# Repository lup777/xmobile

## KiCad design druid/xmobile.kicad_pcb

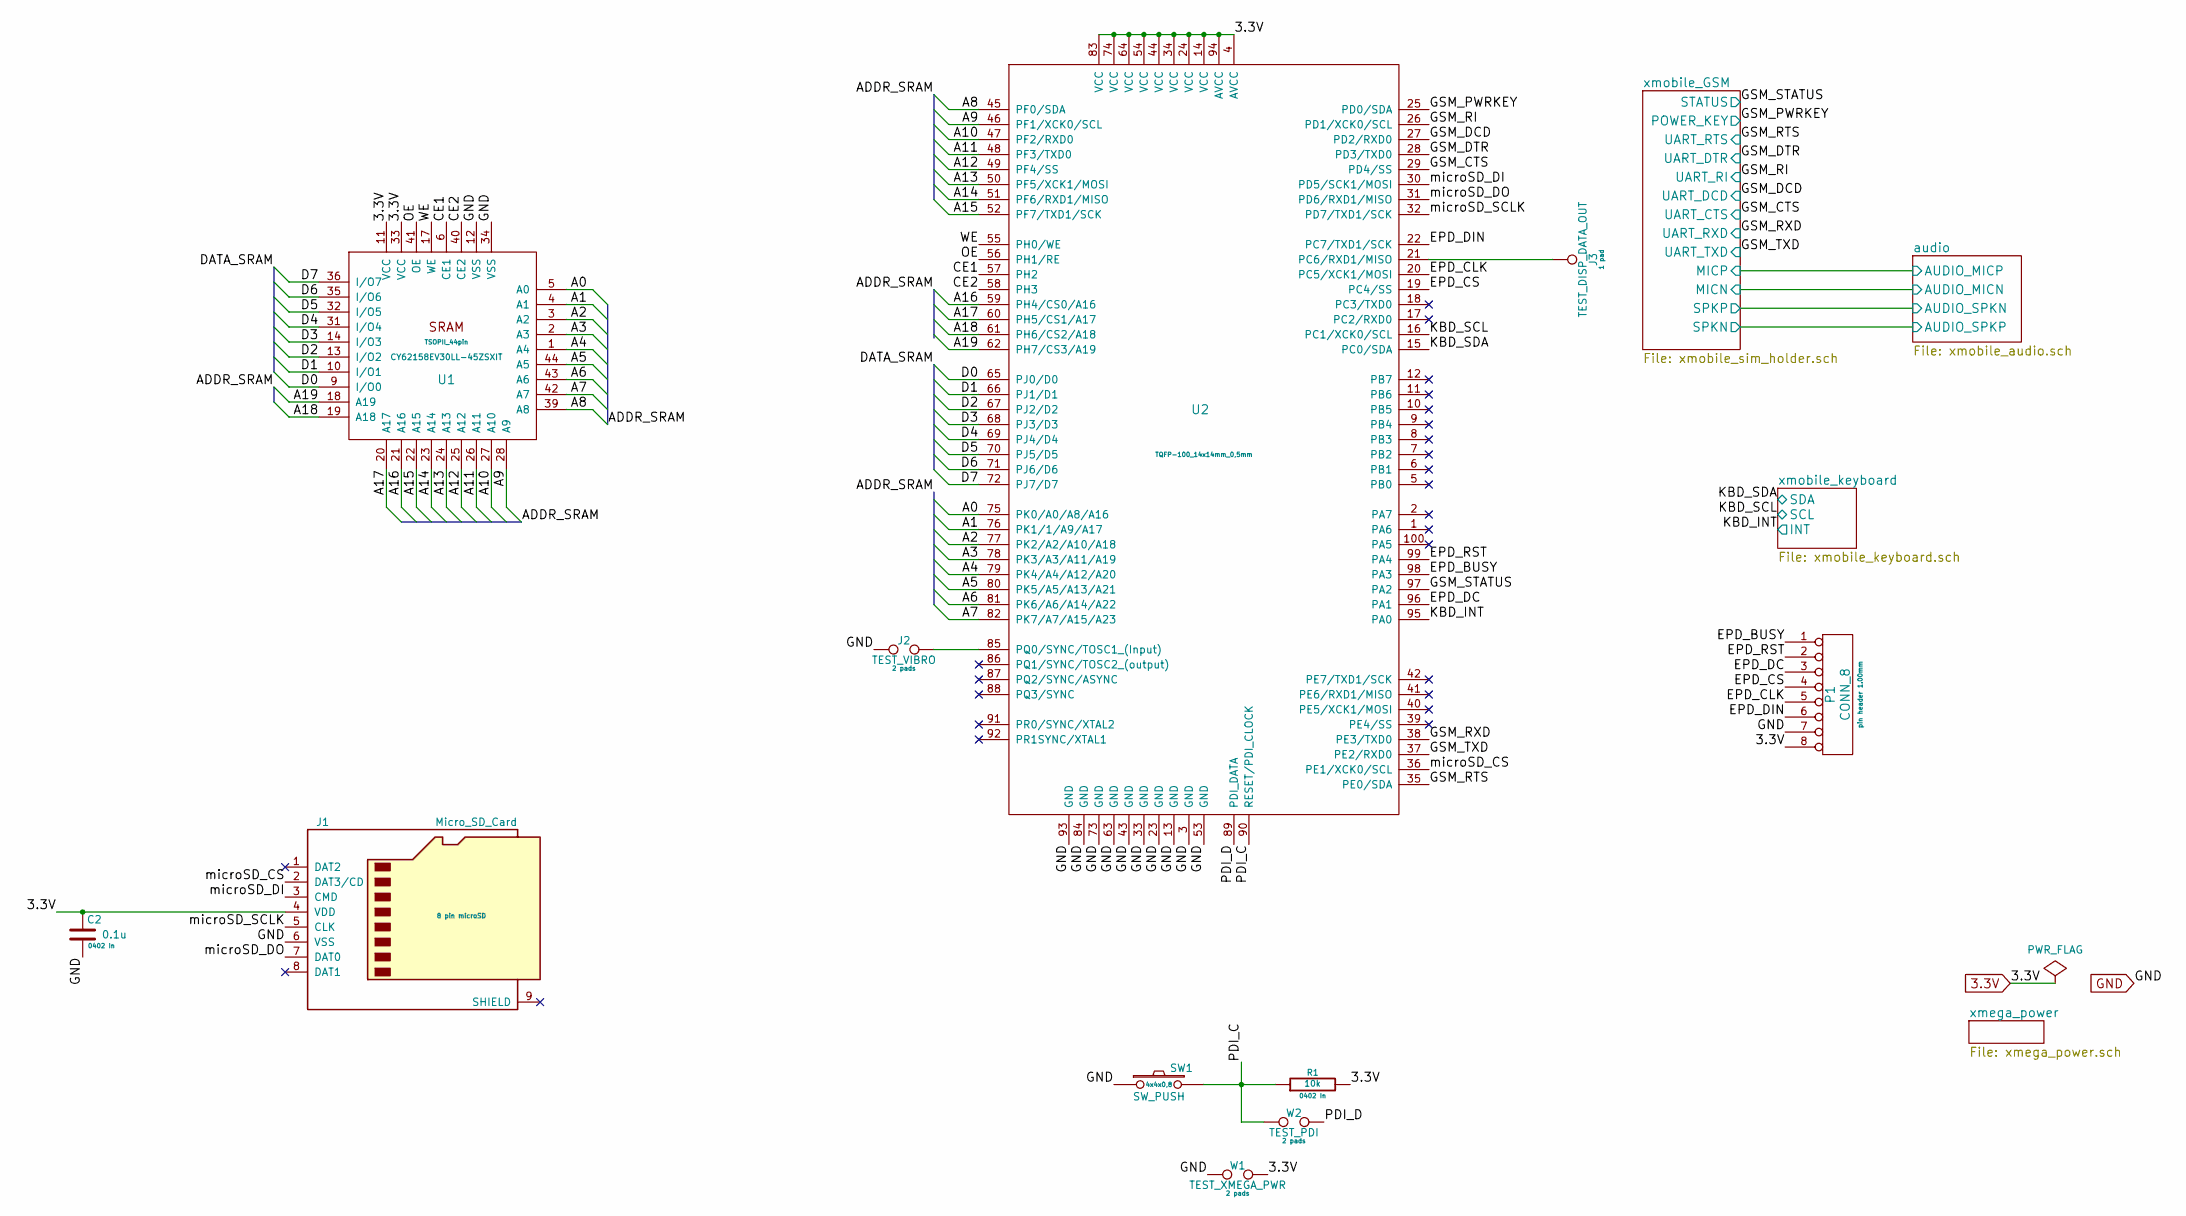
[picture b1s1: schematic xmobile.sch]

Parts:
C2: 0.1u; C_0402_1005Metric
J1: Micro_SD_Card; microSD_HC_Wuerth_693072010801
J2: TEST_VIBRO; TestPoint_2Pads_Pitch2.54mm_Drill0.8mm
J3: TEST_DISP_DATA_OUT; TestPoint_THTPad_1.0x1.0mm_Drill0.5mm
P1: CONN_8; PinHeader_1x08_P1.00mm_Vertical
R1: 10k; R_0402_1005Metric
SW1: SW_PUSH; button_4pin_7,5x5
U1: CY62158EV30LL-45ZSXIT; TSOPII_44_pin
U2: XMega128A1U_TQFP100; TQFP-100_14x14mm_P0.5mm
W1: TEST_XMEGA_PWR; TestPoint_2Pads_Pitch2.54mm_Drill0.8mm
W2: TEST_PDI; TestPoint_2Pads_Pitch2.54mm_Drill0.8mm

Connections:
3.3V: C2.1, J1.4 (VDD), P1.8, R1.2, U1.11 (VCC), U1.33 (VCC), U2.4 (AVCC), U2.14 (VCC), U2.24 (VCC), U2.34 (VCC), U2.44 (VCC), U2.54 (VCC), U2.64 (VCC), U2.74 (VCC), U2.83 (VCC), U2.94 (AVCC), W1.2; also elsewhere on the board
/A0: U1.5 (A0), U2.75 (PK0/A0/A8/A16)
/A1: U1.4 (A1), U2.76 (PK1/1/A9/A17)
/A2: U1.3 (A2), U2.77 (PK2/A2/A10/A18)
/A3: U1.2 (A3), U2.78 (PK3/A3/A11/A19)
/A4: U1.1 (A4), U2.79 (PK4/A4/A12/A20)
/A5: U1.44 (A5), U2.80 (PK5/A5/A13/A21)
/A6: U1.43 (A6), U2.81 (PK6/A6/A14/A22)
/A7: U1.42 (A7), U2.82 (PK7/A7/A15/A23)
/A8: U1.39 (A8), U2.45 (PF0/SDA)
/A9: U1.28 (A9), U2.46 (PF1/XCK0/SCL)
/A10: U1.27 (A10), U2.47 (PF2/RXD0)
/A11: U1.26 (A11), U2.48 (PF3/TXD0)
/A12: U1.25 (A12), U2.49 (PF4/SS)
/A13: U1.24 (A13), U2.50 (PF5/XCK1/MOSI)
/A14: U1.23 (A14), U2.51 (PF6/RXD1/MISO)
/A15: U1.22 (A15), U2.52 (PF7/TXD1/SCK)
/A16: U1.21 (A16), U2.59 (PH4/CS0/A16)
/A17: U1.20 (A17), U2.60 (PH5/CS1/A17)
/A18: U1.19 (A18), U2.61 (PH6/CS2/A18)
/A19: U1.18 (A19), U2.62 (PH7/CS3/A19)
/CE1: U1.6 (CE1), U2.57 (PH2)
/CE2: U1.40 (CE2), U2.58 (PH3)
/D0: U1.9 (I/O0), U2.65 (PJ0/D0)
/D1: U1.10 (I/O1), U2.66 (PJ1/D1)
/D2: U1.13 (I/O2), U2.67 (PJ2/D2)
/D3: U1.14 (I/O3), U2.68 (PJ3/D3)
/D4: U1.31 (I/O4), U2.69 (PJ4/D4)
/D5: U1.32 (I/O5), U2.70 (PJ5/D5)
/D6: U1.35 (I/O6), U2.71 (PJ6/D6)
/D7: U1.36 (I/O7), U2.72 (PJ7/D7)
/EPD_BUSY: P1.1, U2.98 (PA3); also elsewhere on the board
/EPD_CLK: P1.5, U2.20 (PC5/XCK1/MOSI); also elsewhere on the board
/EPD_CS: P1.4, U2.19 (PC4/SS); also elsewhere on the board
/EPD_DC: P1.3, U2.96 (PA1); also elsewhere on the board
/EPD_DIN: P1.6, U2.22 (PC7/TXD1/SCK); also elsewhere on the board
/EPD_RST: P1.2, U2.99 (PA4); also elsewhere on the board
/GSM_CTS: U2.29 (PD4/SS); also elsewhere on the board
/GSM_DCD: U2.27 (PD2/RXD0); also elsewhere on the board
/GSM_DTR: U2.28 (PD3/TXD0); also elsewhere on the board
/GSM_PWRKEY: U2.25 (PD0/SDA); also elsewhere on the board
/GSM_RI: U2.26 (PD1/XCK0/SCL); also elsewhere on the board
/GSM_RTS: U2.35 (PE0/SDA); also elsewhere on the board
/GSM_RXD: U2.38 (PE3/TXD0); also elsewhere on the board
/GSM_STATUS: U2.97 (PA2); also elsewhere on the board
/GSM_TXD: U2.37 (PE2/RXD0); also elsewhere on the board
/KBD_INT: U2.95 (PA0); also elsewhere on the board
/KBD_SCL: U2.16 (PC1/XCK0/SCL); also elsewhere on the board
/KBD_SDA: U2.15 (PC0/SDA); also elsewhere on the board
/OE: U1.41 (OE), U2.56 (PH1/RE)
/PDI_C: R1.1, SW1.2, U2.90 (RESET/PDI_CLOCK), W2.1
/PDI_D: U2.89 (PDI_DATA), W2.2
/WE: U1.17 (WE), U2.55 (PH0/WE)
/microSD_CS: J1.2 (DAT3/CD), U2.36 (PE1/XCK0/SCL)
/microSD_DI: J1.3 (CMD), U2.30 (PD5/SCK1/MOSI)
/microSD_DO: J1.7 (DAT0), U2.31 (PD6/RXD1/MISO)
/microSD_SCLK: J1.5 (CLK), U2.32 (PD7/TXD1/SCK)
GND: C2.2, J1.6 (VSS), J2.1, P1.7, SW1.1, U1.12 (VSS), U1.34 (VSS), U2.3 (GND), U2.13 (GND), U2.23 (GND), U2.33 (GND), U2.43 (GND), U2.53 (GND), U2.63 (GND), U2.73 (GND), U2.84 (GND), U2.93 (GND), W1.1; also elsewhere on the board
unnamed: J2.2, U2.85 (PQ0/SYNC/TOSC1_(Input))
unnamed: J3.1, U2.21 (PC6/RXD1/MISO)

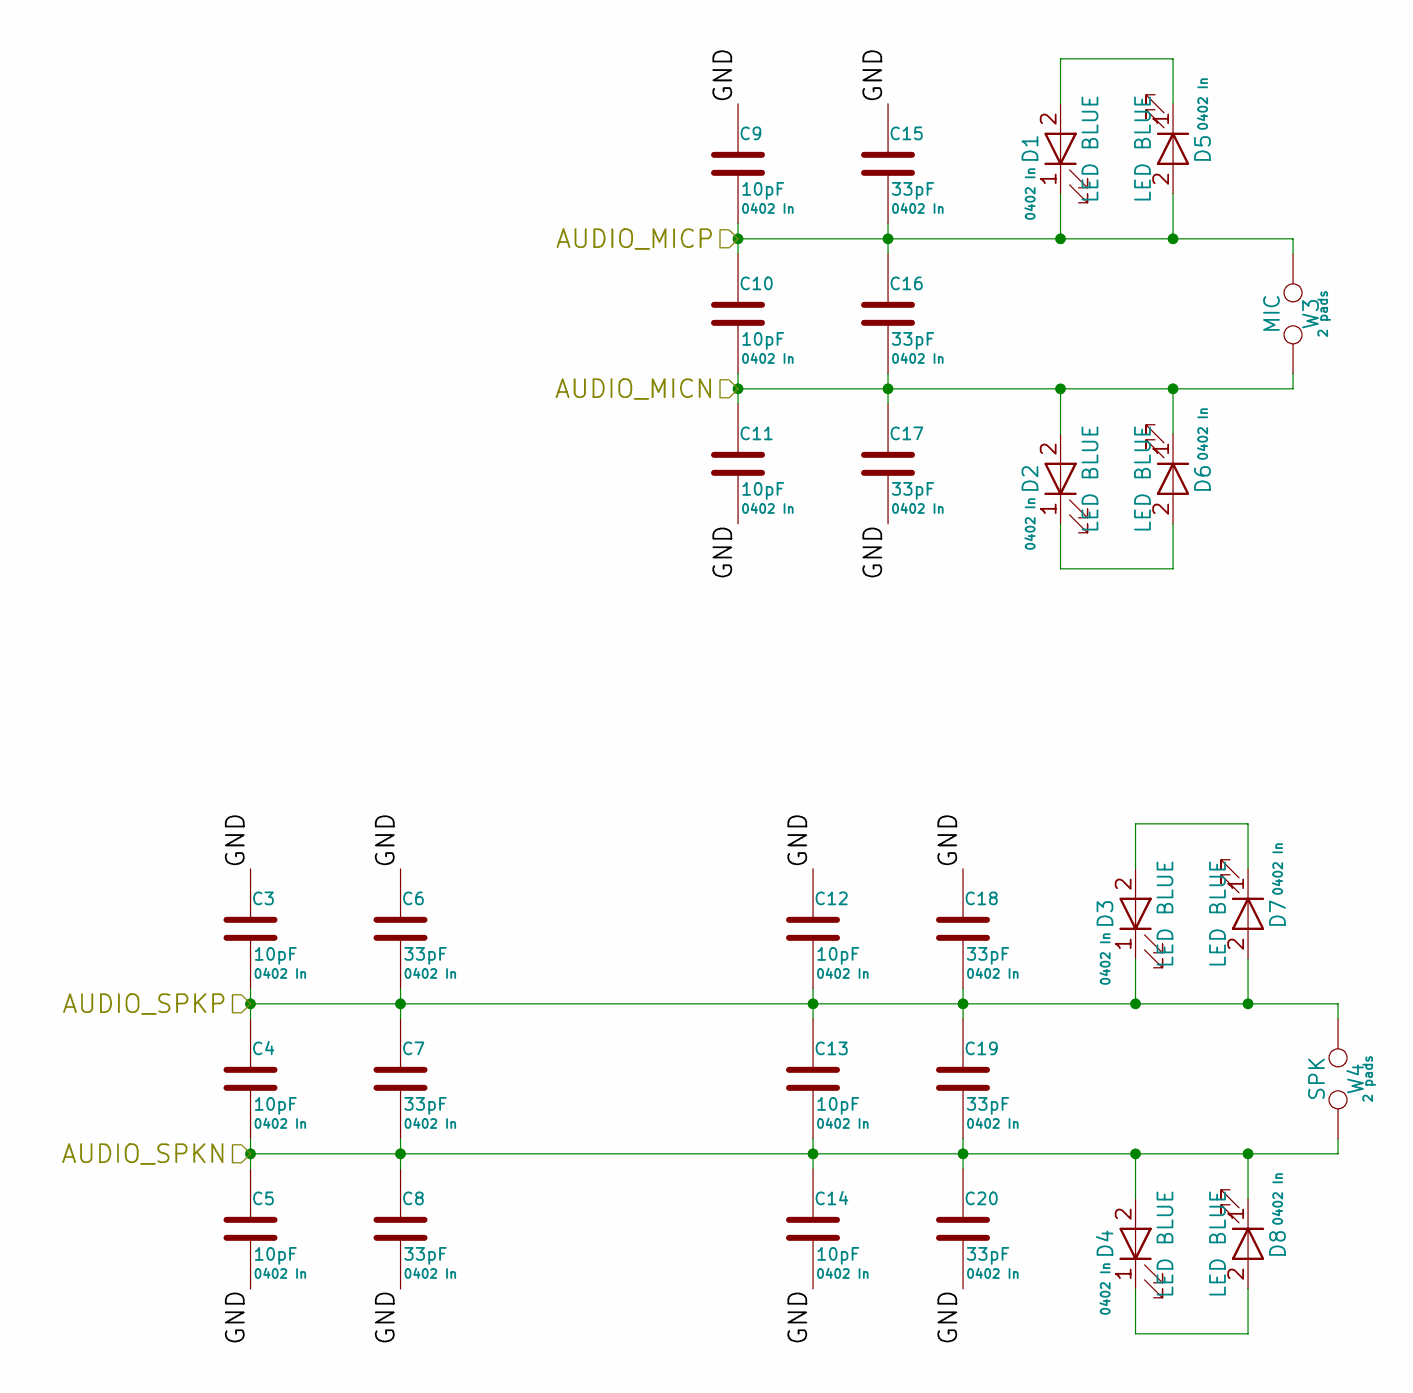
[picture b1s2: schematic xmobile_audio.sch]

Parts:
C3, C4, C5, C9, C10, C11, C12, C13, C14: 10pF; C_0402_1005Metric
C6, C7, C8, C15, C16, C17, C18, C19, C20: 33pF; C_0402_1005Metric
D1, D2, D3, D4, D5, D6, D7, D8: LED BLUE; LED_0402_1005Metric
W3: MIC; TestPoint_2Pads_Pitch2.54mm_Drill0.8mm
W4: SPK; TestPoint_2Pads_Pitch2.54mm_Drill0.8mm

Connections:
/audio/AUDIO_MICN: C10.2, C11.1, C16.2, C17.1, D2.2 (A), D6.1 (K), W3.2; also elsewhere on the board
/audio/AUDIO_MICP: C9.2, C10.1, C15.2, C16.1, D1.1 (K), D5.2 (A), W3.1; also elsewhere on the board
/audio/AUDIO_SPKN: C4.2, C5.1, C7.2, C8.1, C13.2, C14.1, C19.2, C20.1, D4.2 (A), D8.1 (K), W4.2; also elsewhere on the board
/audio/AUDIO_SPKP: C3.2, C4.1, C6.2, C7.1, C12.2, C13.1, C18.2, C19.1, D3.1 (K), D7.2 (A), W4.1; also elsewhere on the board
GND: C3.1, C5.2, C6.1, C8.2, C9.1, C11.2, C12.1, C14.2, C15.1, C17.2, C18.1, C20.2; also elsewhere on the board
unnamed: D1.2 (A), D5.1 (K)
unnamed: D2.1 (K), D6.2 (A)
unnamed: D3.2 (A), D7.1 (K)
unnamed: D4.1 (K), D8.2 (A)

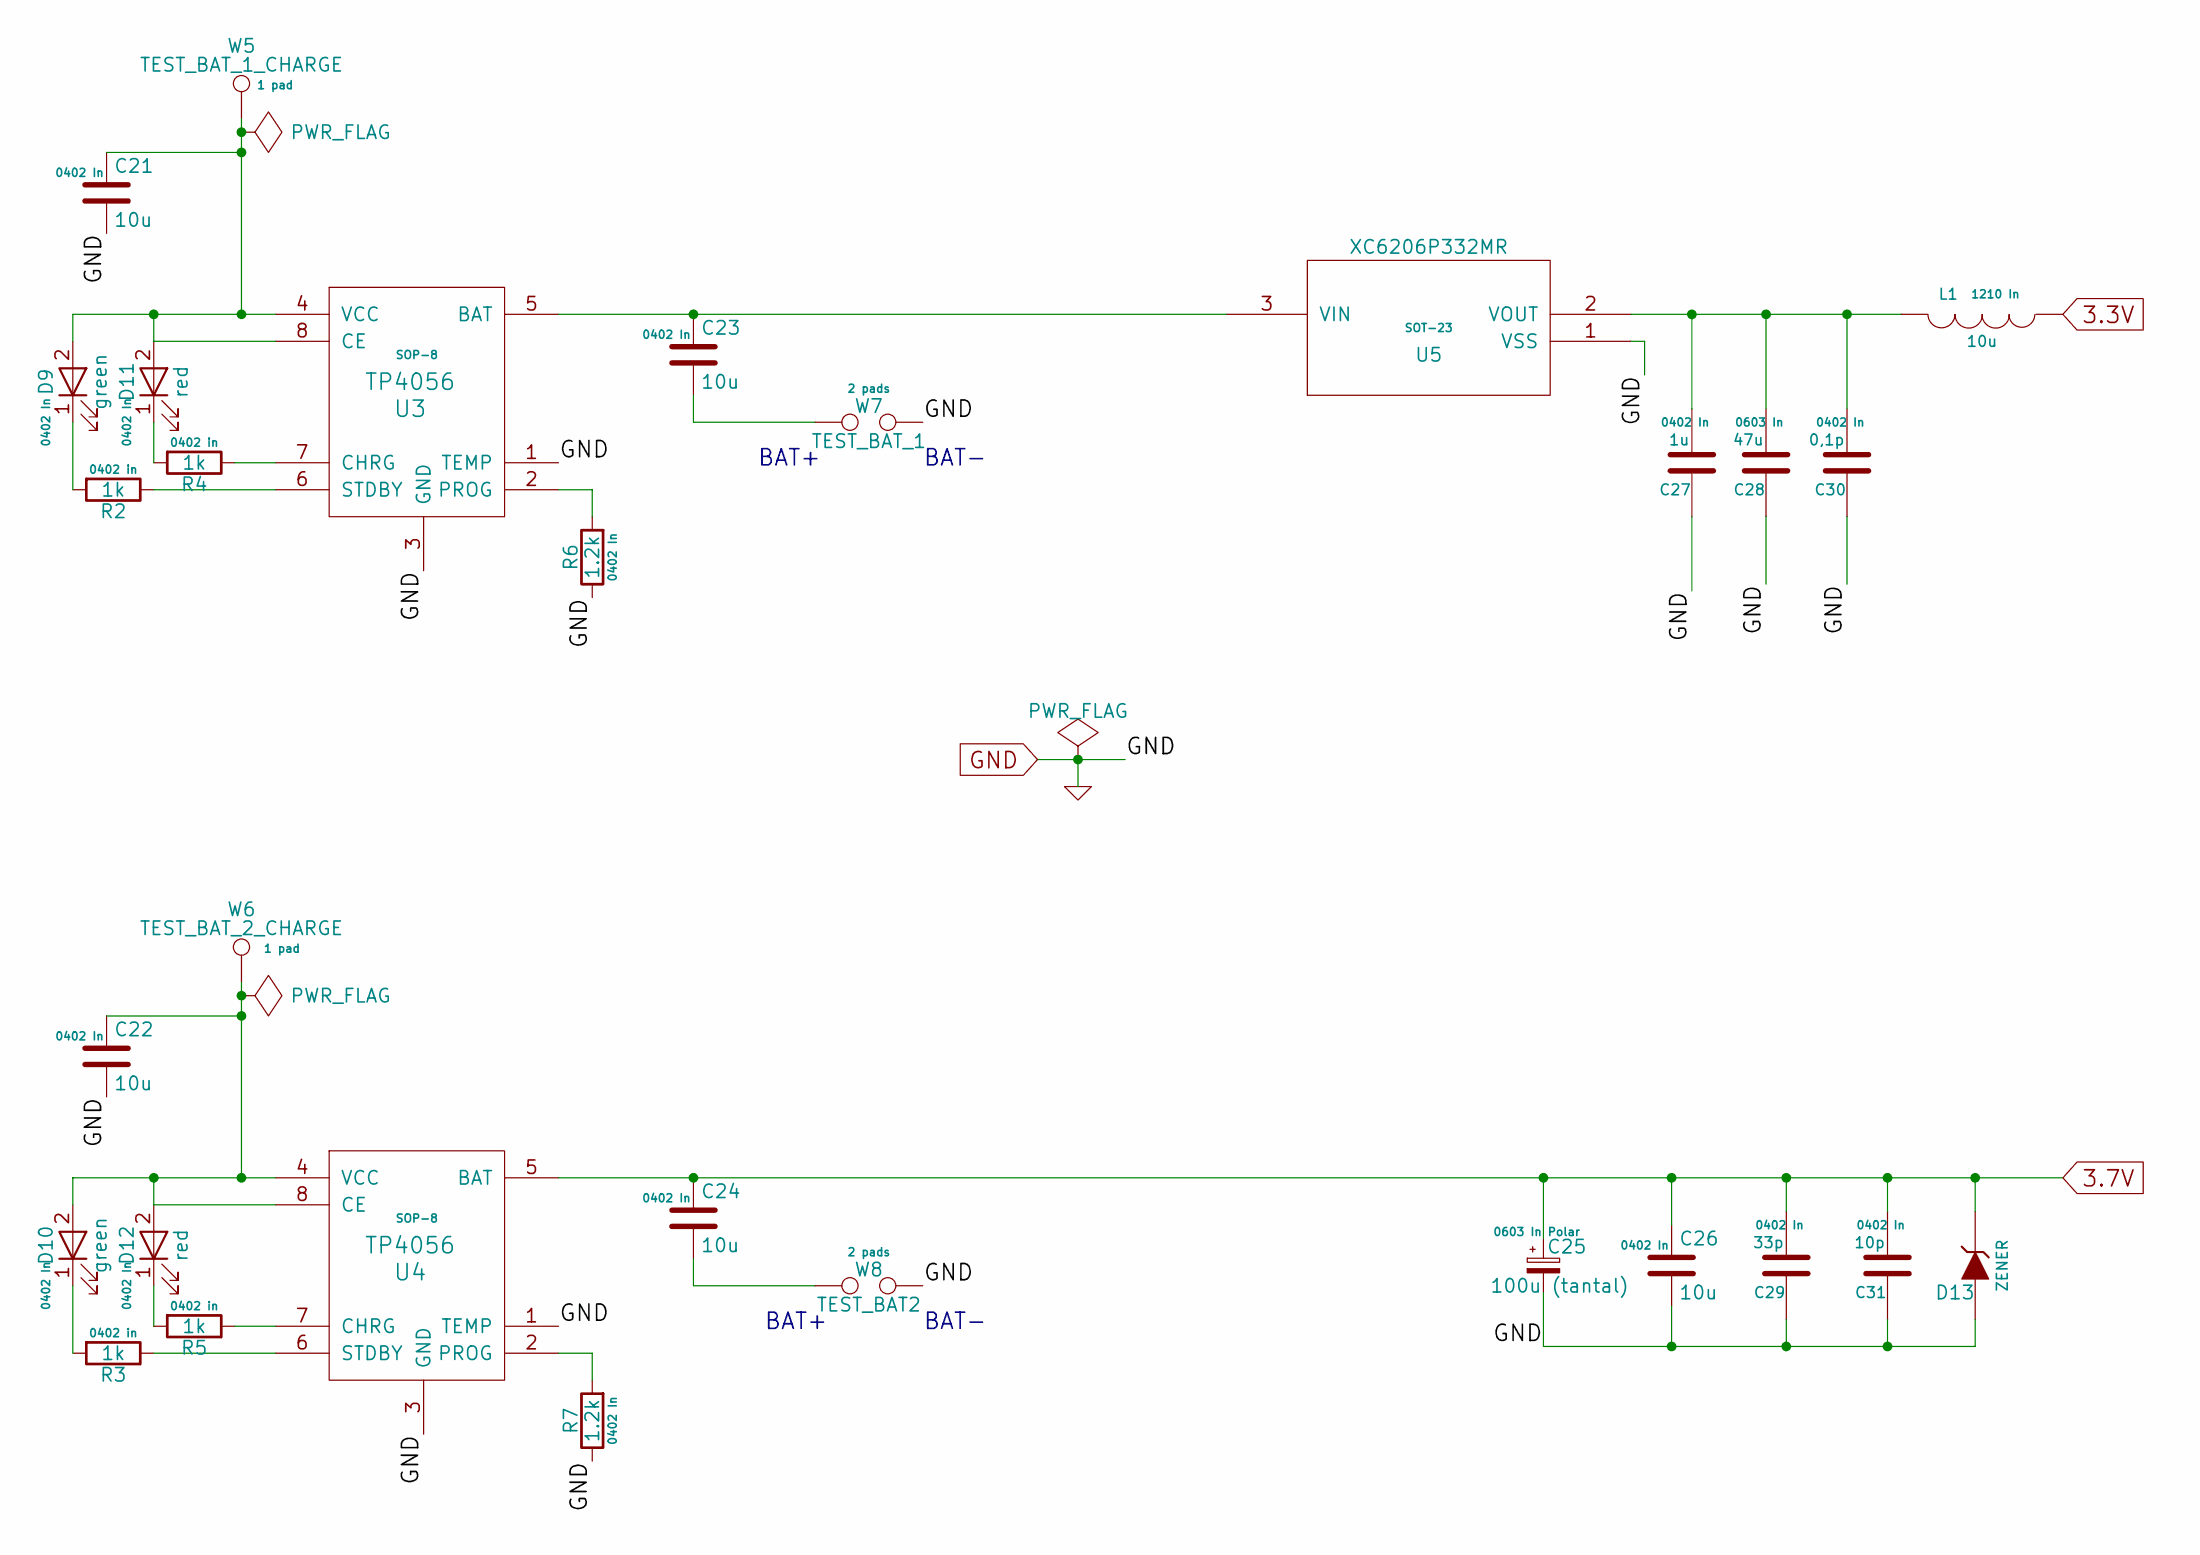
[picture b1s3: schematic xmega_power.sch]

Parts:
C21, C22, C23, C24, C26: 10u; C_0402
C25: 100u (tantal); C_0603
C27: 1u; C_0402
C28: 47u; C_0603
C29: 33p; C_0402
C30: 0,1p; C_0402
C31: 10p; C_0402
D9, D10: green; LED_0402
D11, D12: red; LED_0402
D13: ZENER; SMA_Standard
L1: 10u; I_1210
R2, R3, R4, R5: 1k; R_0402
R6, R7: 1.2k; R_0402
U3, U4: TP4056; SOP8
U5: XC6206P332MR; SOT-23
W5: TEST_BAT_1_CHARGE; Measurement_Point_Square-TH_Small
W6: TEST_BAT_2_CHARGE; Measurement_Point_Square-TH_Small
W7: TEST_BAT_1; Test_Point_2Pads
W8: TEST_BAT2; Test_Point_2Pads

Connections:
3.3V: L1.1; also elsewhere on the board
3.7V: C24.1, C25.1, C26.1, C29.2, C31.2, D13.2 (K), U4.5 (BAT)
GND: C21.2, C22.2, C25.2, C26.2, C27.1, C28.1, C29.1, C30.1, C31.1, D13.1 (A), R6.1, R7.1, U3.1 (TEMP), U3.3 (GND), U4.1 (TEMP), U4.3 (GND), U5.1 (VSS), W7.2, W8.2; also elsewhere on the board
unnamed: C21.1, D9.2 (A), D11.2 (A), U3.4 (VCC), U3.8 (CE), W5.1
unnamed: C22.1, D10.2 (A), D12.2 (A), U4.4 (VCC), U4.8 (CE), W6.1
unnamed: C23.1, U3.5 (BAT), U5.3 (VIN)
unnamed: C23.2, W7.1
unnamed: C24.2, W8.1
unnamed: C27.2, C28.2, C30.2, L1.2, U5.2 (VOUT)
unnamed: D9.1 (K), R2.2
unnamed: D10.1 (K), R3.2
unnamed: D11.1 (K), R4.2
unnamed: D12.1 (K), R5.2
unnamed: R2.1, U3.6 (STDBY)
unnamed: R3.1, U4.6 (STDBY)
unnamed: R4.1, U3.7 (CHRG)
unnamed: R5.1, U4.7 (CHRG)
unnamed: R6.2, U3.2 (PROG)
unnamed: R7.2, U4.2 (PROG)

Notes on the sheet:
BAT-
BAT+

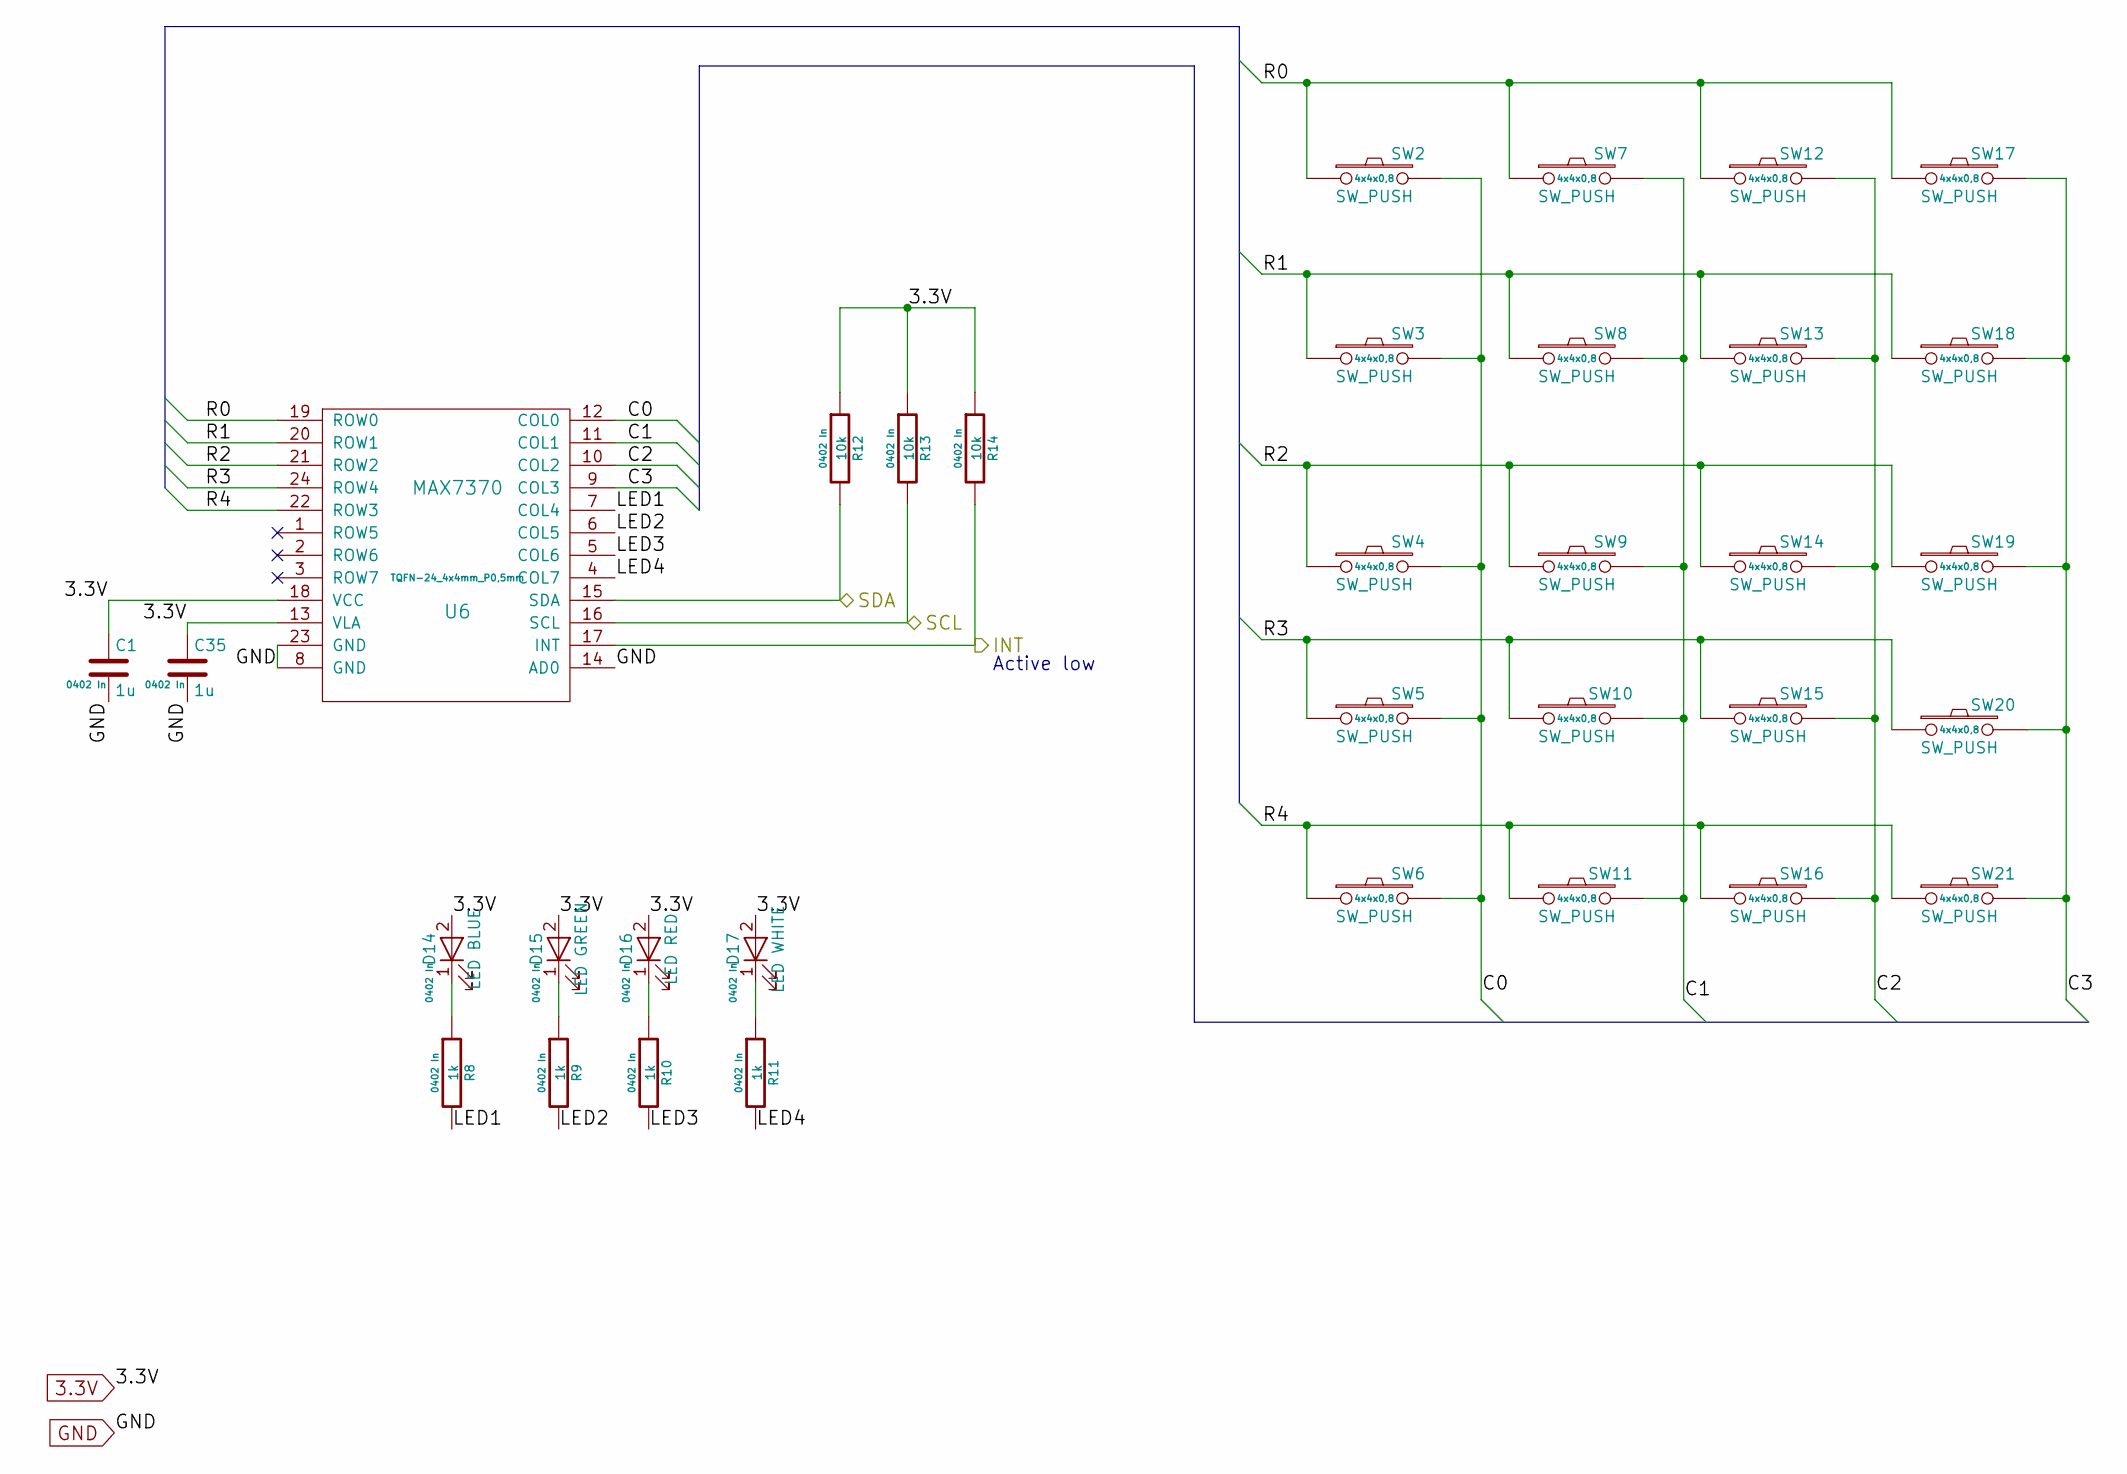
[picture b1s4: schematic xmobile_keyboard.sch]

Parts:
C1, C35: 1u; C_0402_1005Metric
D14: LED BLUE; LED_0402_1005Metric
D15: LED GREEN; LED_0402_1005Metric
D16: LED RED; LED_0402_1005Metric
D17: LED WHITE; LED_0402_1005Metric
R8, R9, R10, R11: 1k; R_0402_1005Metric
R12, R13, R14: 10k; R_0402_1005Metric
SW2, SW3, SW4, SW5, SW6, SW7, SW8, SW9, SW10, SW11, SW12, SW13, SW14, SW15, SW16, SW17, SW18, SW19, SW20, SW21: SW_PUSH; button_4pin_7,5x5
U6: MAX7370; QFN-24-1EP_4x4mm_P0.5mm_EP2.7x2.7mm

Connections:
3.3V: C1.1, C35.1, D14.2 (A), D15.2 (A), D16.2 (A), D17.2 (A), R12.1, R13.1, R14.1, U6.13 (VLA), U6.18 (VCC); also elsewhere on the board
/KBD_INT: R14.2, U6.17 (INT); also elsewhere on the board
/KBD_SCL: R13.2, U6.16 (SCL); also elsewhere on the board
/KBD_SDA: R12.2, U6.15 (SDA); also elsewhere on the board
/xmobile_keyboard/C0: SW2.2, SW3.2, SW4.2, SW5.2, SW6.2, U6.12 (COL0)
/xmobile_keyboard/C1: SW7.2, SW8.2, SW9.2, SW10.2, SW11.2, U6.11 (COL1)
/xmobile_keyboard/C2: SW12.2, SW13.2, SW14.2, SW15.2, SW16.2, U6.10 (COL2)
/xmobile_keyboard/C3: SW17.2, SW18.2, SW19.2, SW20.2, SW21.2, U6.9 (COL3)
/xmobile_keyboard/LED1: R8.2, U6.7 (COL4)
/xmobile_keyboard/LED2: R9.2, U6.6 (COL5)
/xmobile_keyboard/LED3: R10.2, U6.5 (COL6)
/xmobile_keyboard/LED4: R11.2, U6.4 (COL7)
/xmobile_keyboard/R0: SW2.1, SW7.1, SW12.1, SW17.1, U6.19 (ROW0)
/xmobile_keyboard/R1: SW3.1, SW8.1, SW13.1, SW18.1, U6.20 (ROW1)
/xmobile_keyboard/R2: SW4.1, SW9.1, SW14.1, SW19.1, U6.21 (ROW2)
/xmobile_keyboard/R3: SW5.1, SW10.1, SW15.1, SW20.1, U6.24 (ROW4)
/xmobile_keyboard/R4: SW6.1, SW11.1, SW16.1, SW21.1, U6.22 (ROW3)
GND: C1.2, C35.2, U6.8 (GND), U6.14 (AD0), U6.23 (GND); also elsewhere on the board
unnamed: D14.1 (K), R8.1
unnamed: D15.1 (K), R9.1
unnamed: D16.1 (K), R10.1
unnamed: D17.1 (K), R11.1

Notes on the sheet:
Active low

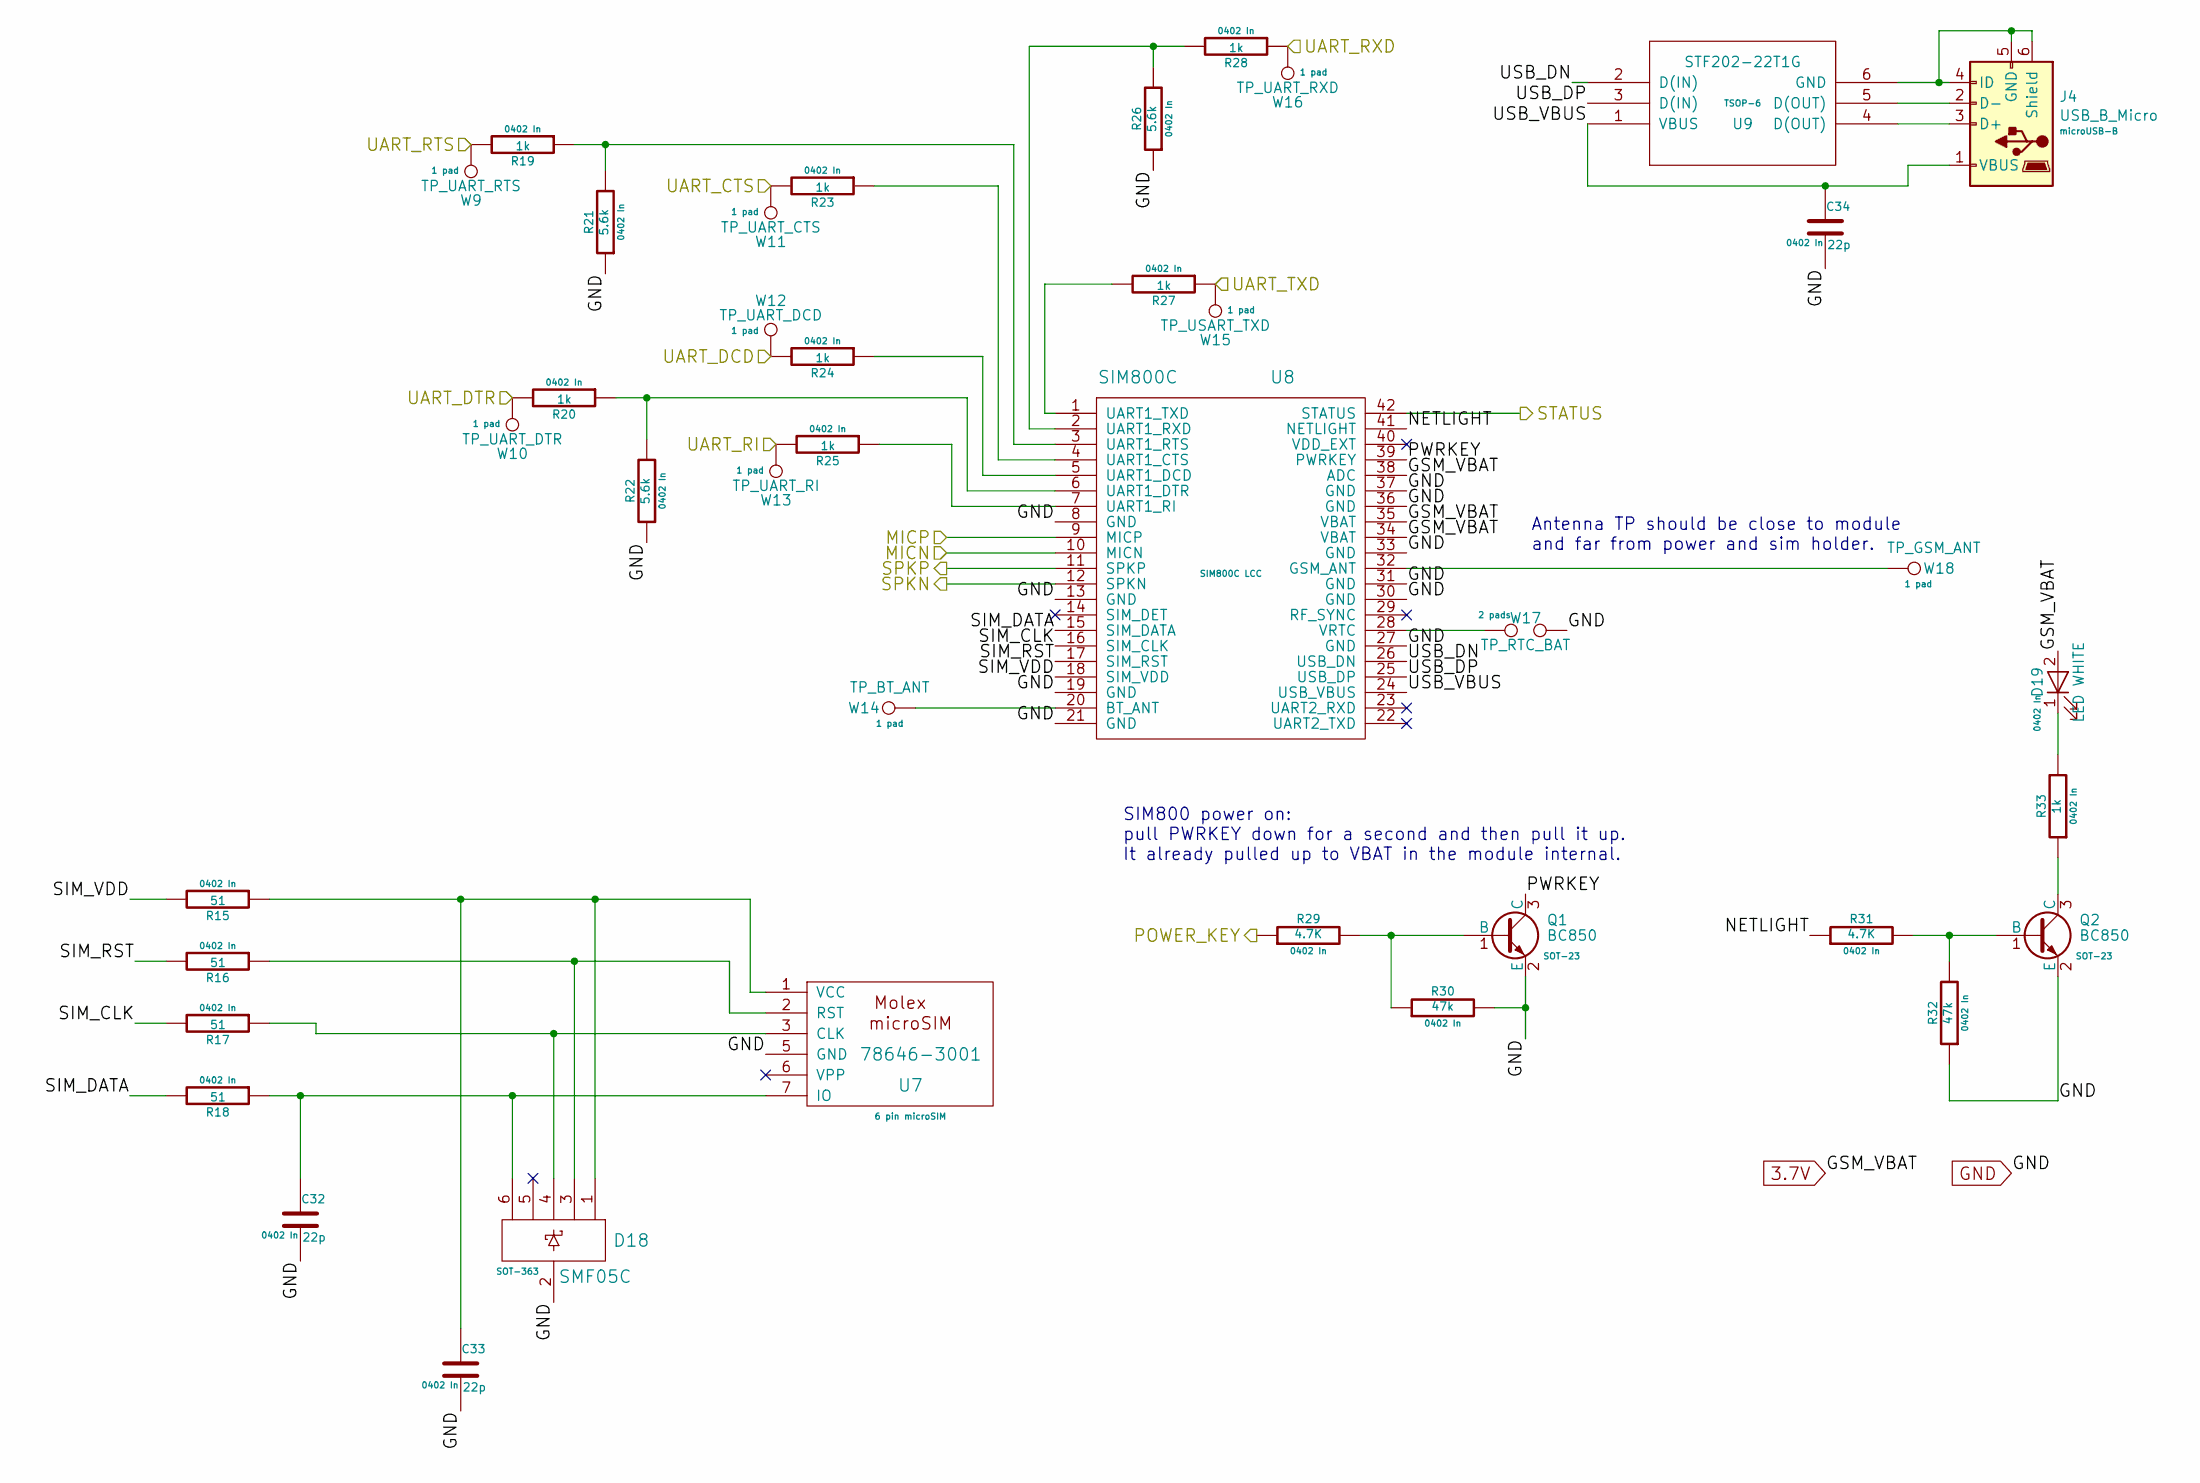
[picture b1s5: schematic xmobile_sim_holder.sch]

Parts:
C32, C33, C34: 22p; C_0402_1005Metric
D18: SMF05C; SOT-363_SC-70-6
D19: LED WHITE; LED_0402_1005Metric
J4: USB_B_Micro; USB_Micro-B_Molex_47346-0001
Q1, Q2: BC850; SOT-23
R15, R16, R17, R18: 51; R_0402_1005Metric
R19, R20, R23, R24, R25, R27, R28, R33: 1k; R_0402_1005Metric
R21, R22, R26: 5.6k; R_0402_1005Metric
R29, R31: 4.7K; R_0402_1005Metric
R30, R32: 47k; R_0402_1005Metric
U7: 78646-3001; molex-microSIM_SD-78646-001
U8: SIM800C
U9: STF202-22T1G; TSOP-6_CASE-318G-02
W9: TP_UART_RTS; TestPoint_THTPad_1.0x1.0mm_Drill0.5mm
W10: TP_UART_DTR; TestPoint_THTPad_1.0x1.0mm_Drill0.5mm
W11: TP_UART_CTS; TestPoint_THTPad_1.0x1.0mm_Drill0.5mm
W12: TP_UART_DCD; TestPoint_THTPad_1.0x1.0mm_Drill0.5mm
W13: TP_UART_RI; TestPoint_THTPad_1.0x1.0mm_Drill0.5mm
W14: TP_BT_ANT; TestPoint_THTPad_1.0x1.0mm_Drill0.5mm
W15: TP_USART_TXD; TestPoint_THTPad_1.0x1.0mm_Drill0.5mm
W16: TP_UART_RXD; TestPoint_THTPad_1.0x1.0mm_Drill0.5mm
W17: TP_RTC_BAT; TestPoint_2Pads_Pitch2.54mm_Drill0.8mm
W18: TP_GSM_ANT; TestPoint_THTPad_1.0x1.0mm_Drill0.5mm

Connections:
/GSM_CTS: R23.2, W11.1; also elsewhere on the board
/GSM_DCD: R24.2, W12.1; also elsewhere on the board
/GSM_DTR: R20.2, W10.1; also elsewhere on the board
/GSM_PWRKEY: R29.1; also elsewhere on the board
/GSM_RI: R25.2, W13.1; also elsewhere on the board
/GSM_RTS: R19.2, W9.1; also elsewhere on the board
/GSM_RXD: R28.1, W16.1; also elsewhere on the board
/GSM_STATUS: U8.42 (STATUS); also elsewhere on the board
/GSM_TXD: R27.1, W15.1; also elsewhere on the board
/audio/AUDIO_MICN: U8.10 (MICN); also elsewhere on the board
/audio/AUDIO_MICP: U8.9 (MICP); also elsewhere on the board
/audio/AUDIO_SPKN: U8.11 (SPKP); also elsewhere on the board
/audio/AUDIO_SPKP: U8.12 (SPKN); also elsewhere on the board
/xmobile_GSM/GSM_VBAT: D19.2 (A), U8.34 (VBAT), U8.35 (VBAT), U8.38 (ADC)
/xmobile_GSM/NETLIGHT: R31.1, U8.41 (NETLIGHT)
/xmobile_GSM/PWRKEY: Q1.3 (C), U8.39 (PWRKEY)
/xmobile_GSM/SIM_CLK: R17.2, U8.16 (SIM_CLK)
/xmobile_GSM/SIM_DATA: R18.2, U8.15 (SIM_DATA)
/xmobile_GSM/SIM_RST: R16.2, U8.17 (SIM_RST)
/xmobile_GSM/SIM_VDD: R15.2, U8.18 (SIM_VDD)
/xmobile_GSM/USB_DN: U8.26 (USB_DN), U9.2 (D(IN))
/xmobile_GSM/USB_DP: U8.25 (USB_DP), U9.3 (D(IN))
/xmobile_GSM/USB_VBUS: C34.1, J4.1 (VBUS), U8.24 (USB_VBUS), U9.1 (VBUS)
GND: C32.2, C33.2, C34.2, D18.2, Q1.2 (E), Q2.2 (E), R21.1, R22.1, R26.1, R30.2, R32.1, U7.5 (GND), U8.8 (GND), U8.13 (GND), U8.19 (GND), U8.21 (GND), U8.27 (GND), U8.30 (GND), U8.31 (GND), U8.33 (GND), U8.36 (GND), U8.37 (GND), W17.2; also elsewhere on the board
unnamed: C32.1, D18.6, R18.1, U7.7 (IO)
unnamed: C33.1, D18.1, R15.1, U7.1 (VCC)
unnamed: D18.3, R16.1, U7.2 (RST)
unnamed: D18.4, R17.1, U7.3 (CLK)
unnamed: D19.1 (K), R33.2
unnamed: J4.2 (D-), U9.5 (D(OUT))
unnamed: J4.3 (D+), U9.4 (D(OUT))
unnamed: J4.4 (ID), J4.5 (GND), J4.6 (Shield), U9.6 (GND)
unnamed: Q1.1 (B), R29.2, R30.1
unnamed: Q2.1 (B), R31.2, R32.2
unnamed: Q2.3 (C), R33.1
unnamed: R19.1, R21.2, U8.3 (UART1_RTS)
unnamed: R20.1, R22.2, U8.6 (UART1_DTR)
unnamed: R23.1, U8.4 (UART1_CTS)
unnamed: R24.1, U8.5 (UART1_DCD)
unnamed: R25.1, U8.7 (UART1_RI)
unnamed: R26.2, R28.2, U8.2 (UART1_RXD)
unnamed: R27.2, U8.1 (UART1_TXD)
unnamed: U8.20 (BT_ANT), W14.1
unnamed: U8.28 (VRTC), W17.1
unnamed: U8.32 (GSM_ANT), W18.1

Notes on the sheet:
SIM800 power on: pull PWRKEY down for a second and then pull it up. It already pulled up to VBAT in the module internal.
Antenna TP should be close to module and far from power and sim holder.
